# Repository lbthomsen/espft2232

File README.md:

# espft2232
Esp32 Dev Board FT-2232 Breakout Board

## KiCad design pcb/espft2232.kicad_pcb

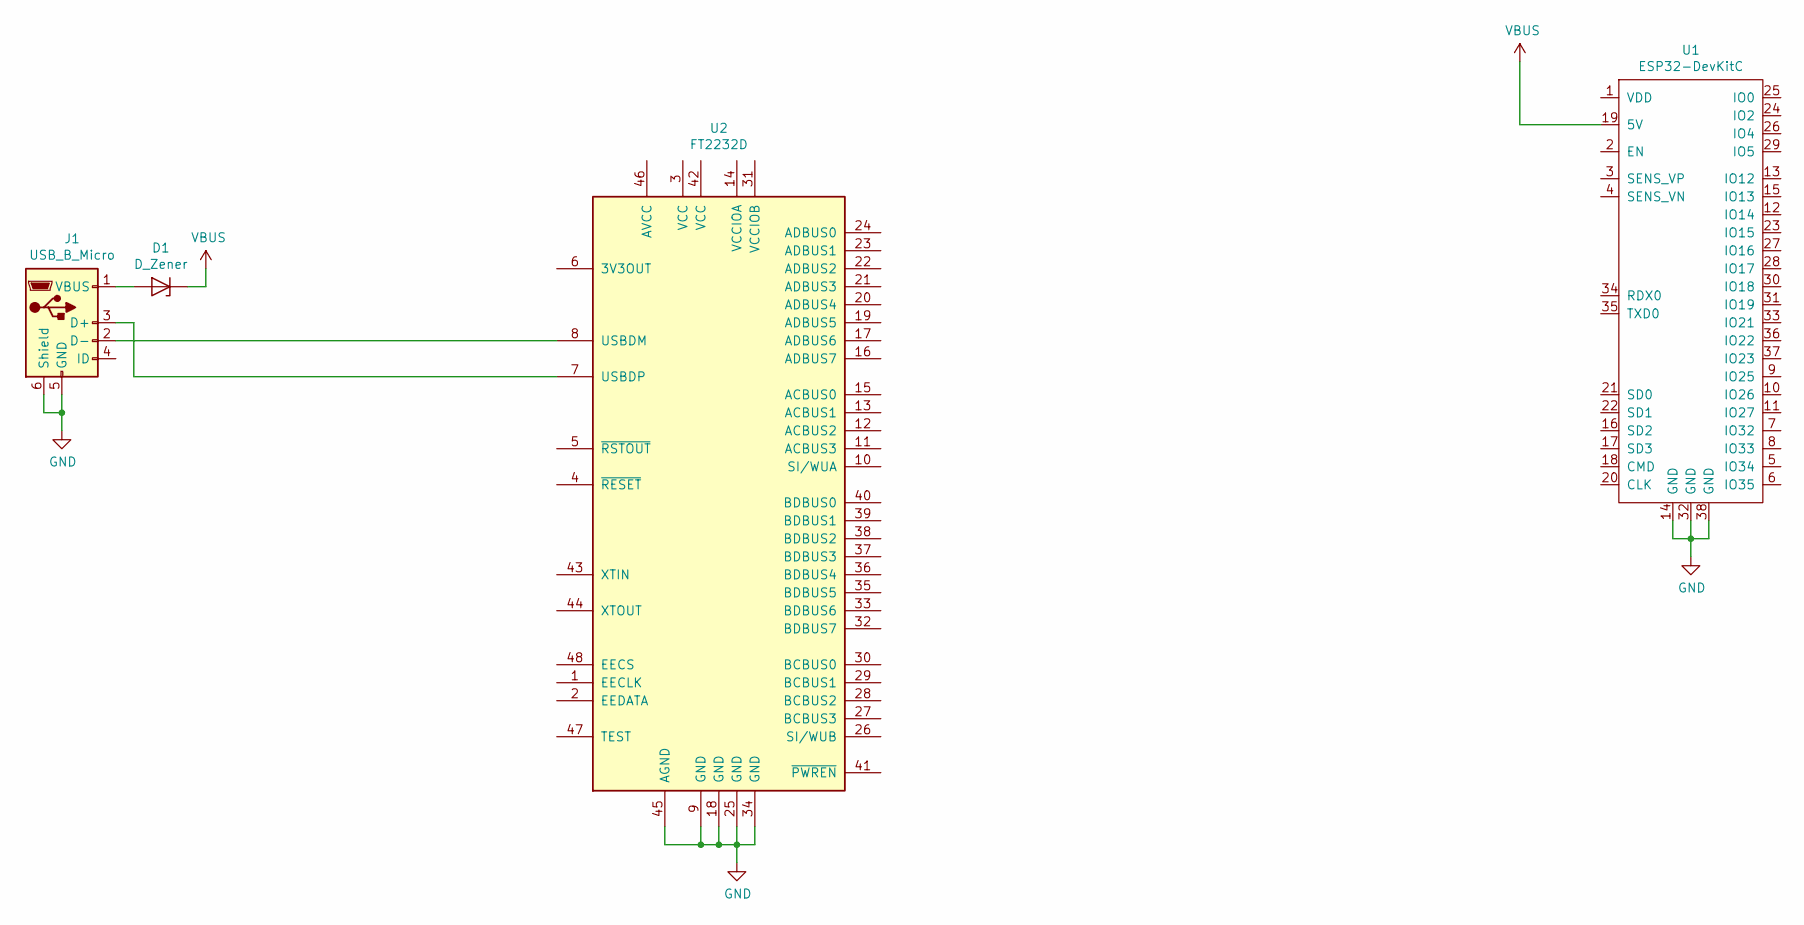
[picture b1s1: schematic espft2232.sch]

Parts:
D1: D_Zener; D_0603_1608Metric
J1: USB_B_Micro; USB_Micro-B_Molex-105017-0001
U1: ESP32-DevKitC
U2: FT2232D; LQFP-48_7x7mm_P0.5mm

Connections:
GND: J1.5 (GND), J1.6 (Shield), U1.14 (GND), U1.32 (GND), U1.38 (GND), U2.9 (GND), U2.18 (GND), U2.25 (GND), U2.34 (GND), U2.45 (AGND)
unnamed: D1.2 (A), J1.1 (VBUS)
unnamed: J1.2 (D-), U2.8 (USBDM)
unnamed: J1.3 (D+), U2.7 (USBDP)
VBUS: D1.1 (K), U1.19 (5V)

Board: 2 copper layers, 4 parts (0 on the bottom side), 5 nets, no tracks yet.

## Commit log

2019-05-24 Started
